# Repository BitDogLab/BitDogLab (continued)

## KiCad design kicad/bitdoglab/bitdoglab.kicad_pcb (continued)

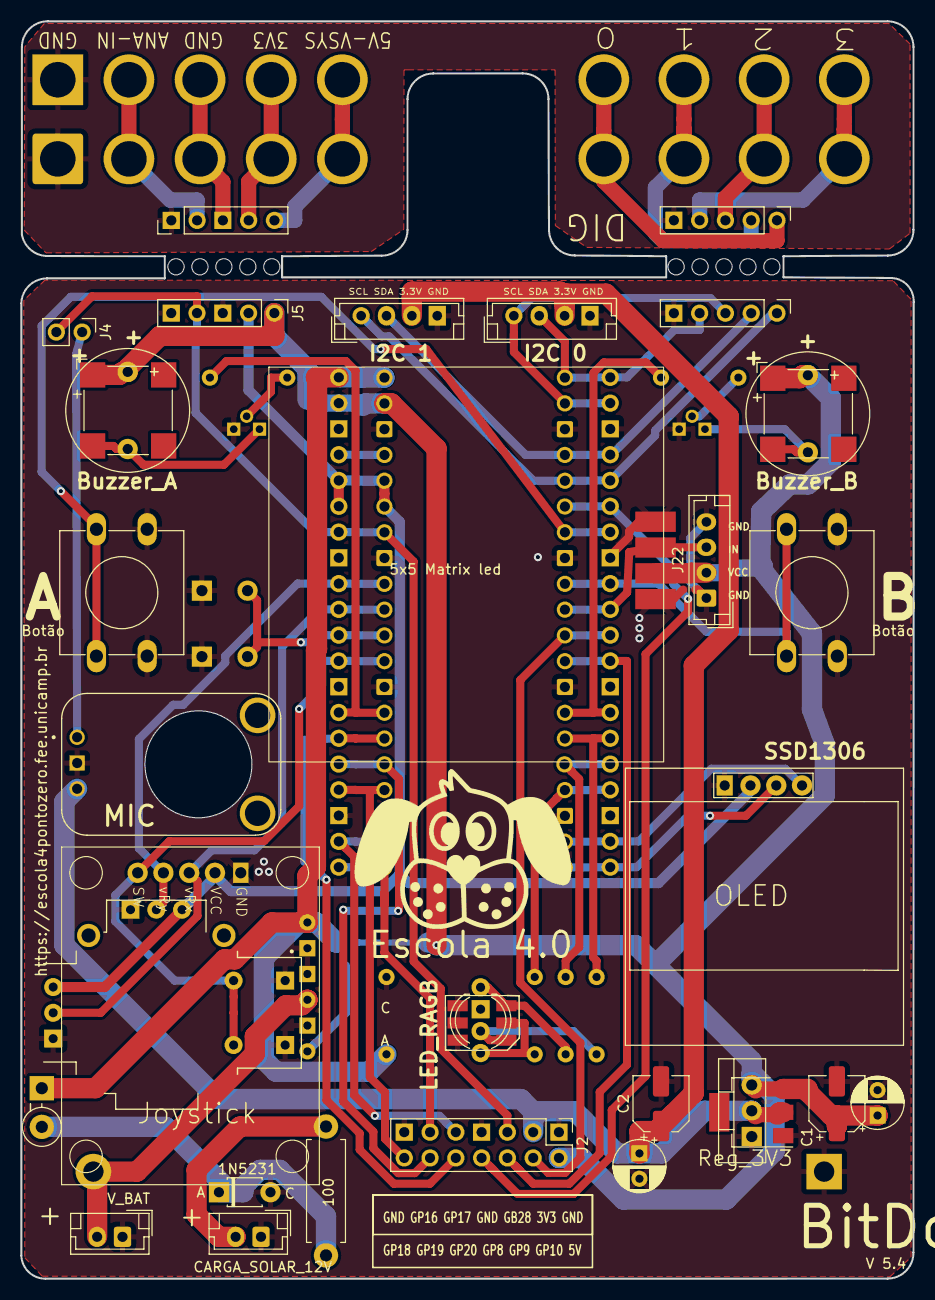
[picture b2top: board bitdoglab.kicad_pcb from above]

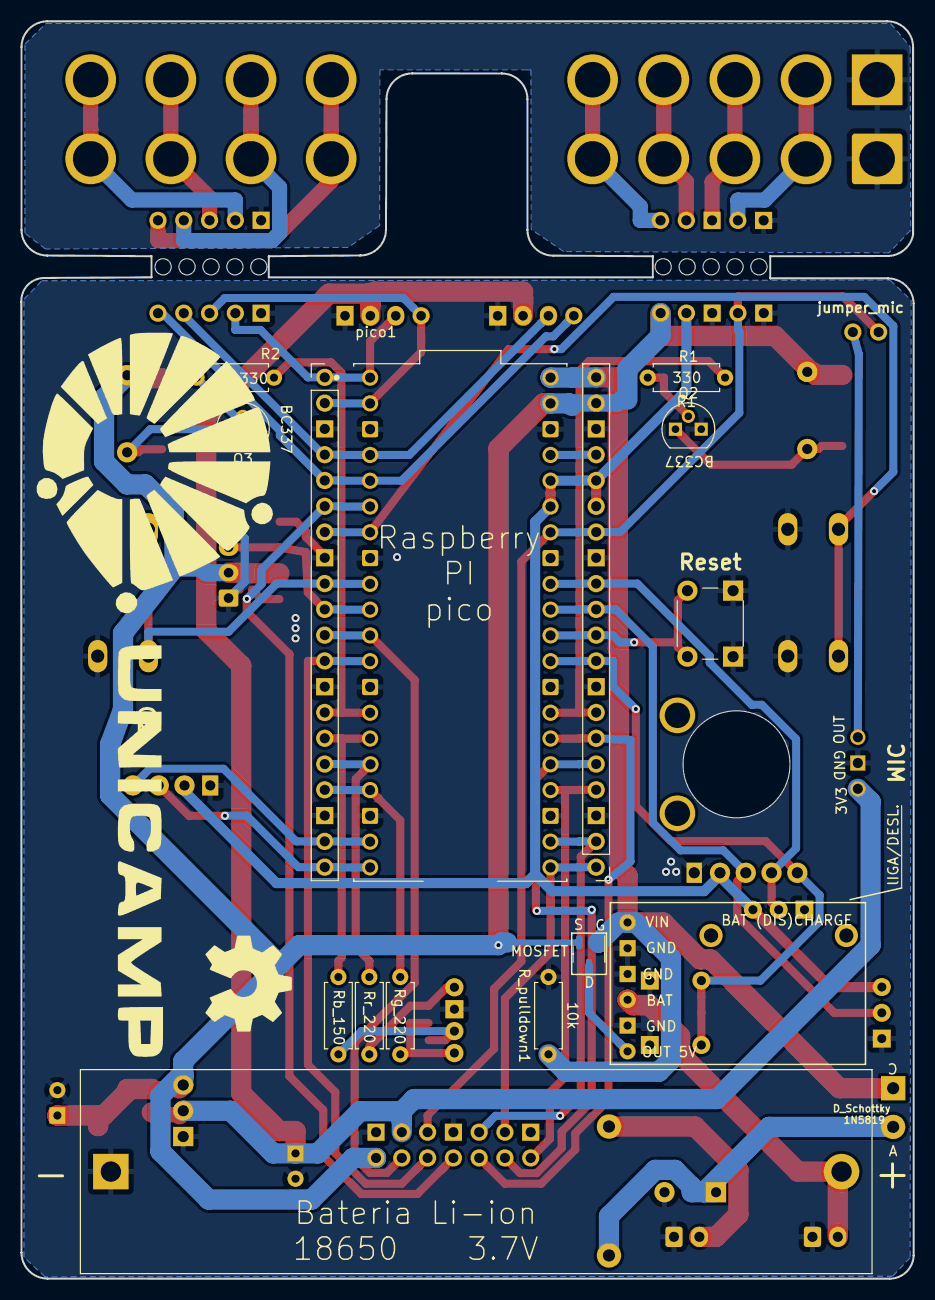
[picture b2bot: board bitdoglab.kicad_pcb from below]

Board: 2 copper layers, 87.9 x 123.9 mm, 60 parts (17 on the bottom side), 54 nets.

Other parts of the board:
G1: LOGO; logo bitDog 25mm
G2: LOGO; unicamp V2A
G3: LOGO
JOY1: JOYSTICK; XDCR_COM-09032

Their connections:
3.3_OUT: JOY1.H1, JOY1.V1; also elsewhere on the board
/pino_29: JOY1.B2A, JOY1.B2B; also elsewhere on the board
/pino_31: JOY1.H2; also elsewhere on the board
/pino_32: JOY1.V2; also elsewhere on the board
GNDREF: JOY1.B1A, JOY1.B1B, JOY1.H3, JOY1.V3; also elsewhere on the board

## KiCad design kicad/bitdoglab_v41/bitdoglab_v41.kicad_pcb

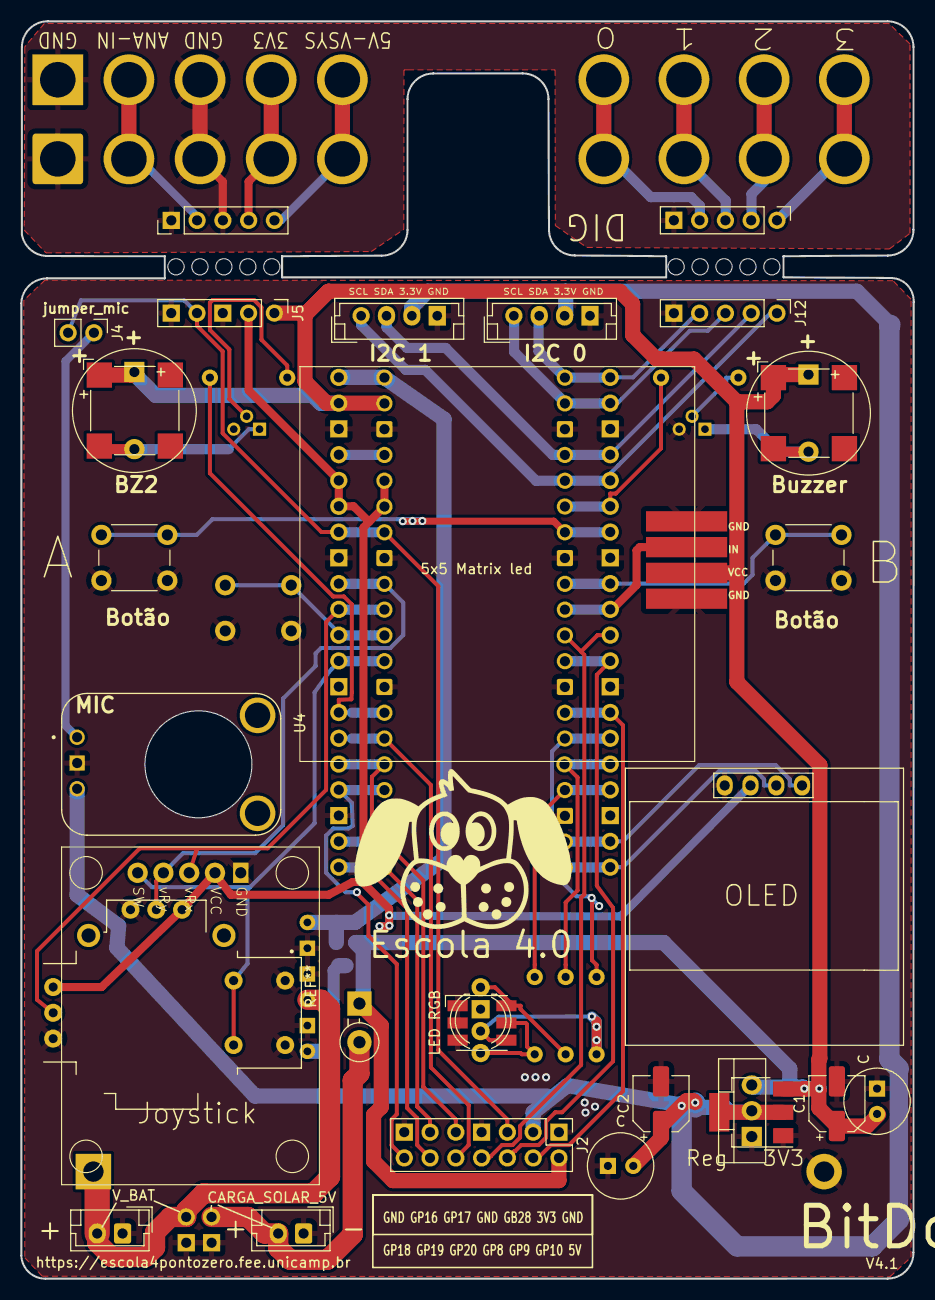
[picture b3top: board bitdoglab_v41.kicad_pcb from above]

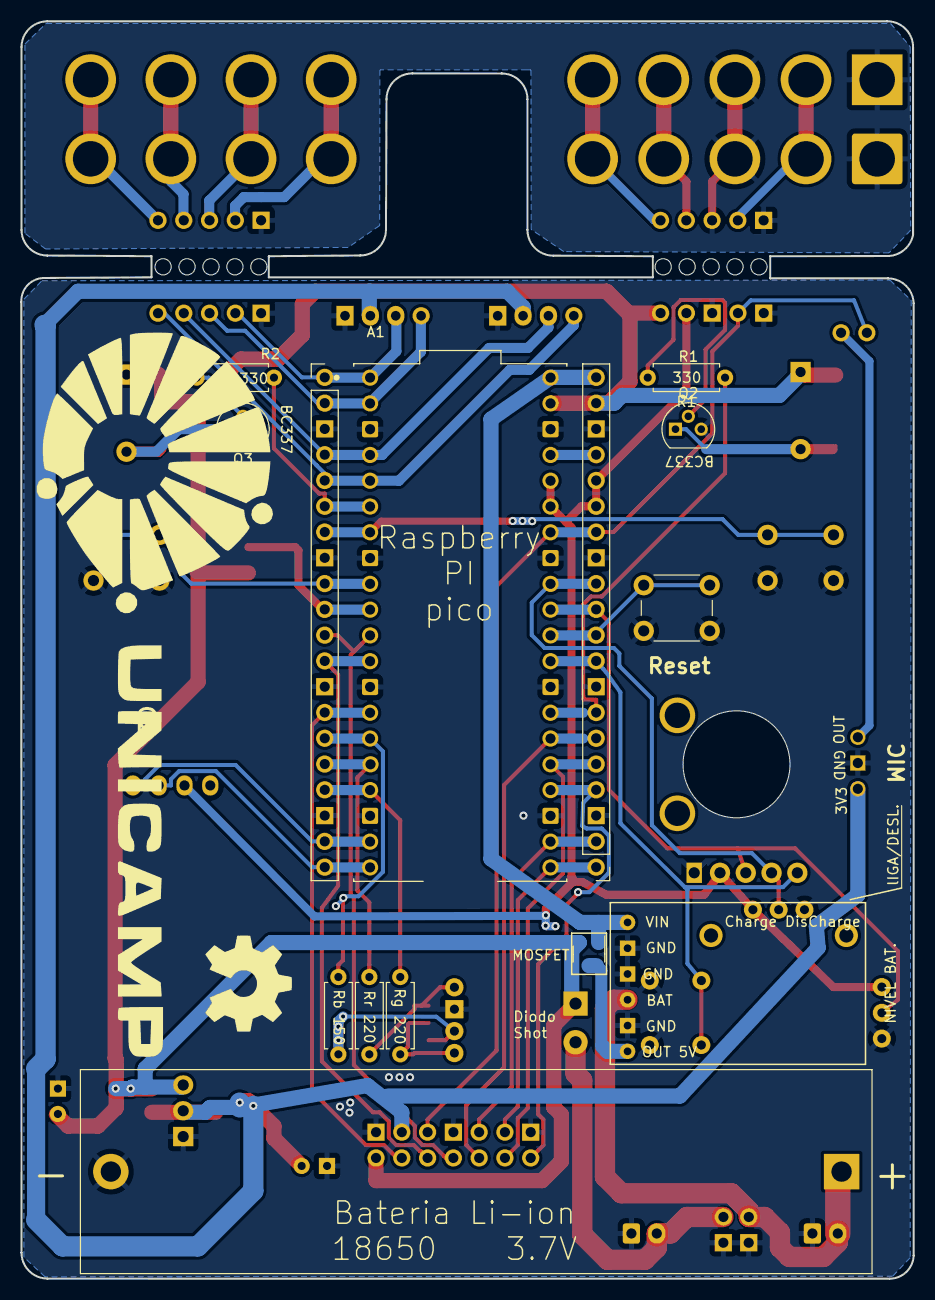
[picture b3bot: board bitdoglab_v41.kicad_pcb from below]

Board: 2 copper layers, 87.9 x 123.9 mm, 59 parts (16 on the bottom side), 52 nets.

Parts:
A1: SC0918; MODULE_SC0918
BT1: Battery_Cell; BatteryHolder_MPD_BH-18650-PC2
BZ1: Buzzer_A; Buzzer_12x9.5RM7.6
BZ2: Buzzer_A_SMD; MagneticBuzzer_CUI_CMT-8504-100-SMT
BZ3: Buzzer_B; Buzzer_12x9.5RM7.6
BZ4: Buzzer_B_SMD; MagneticBuzzer_CUI_CMT-8504-100-SMT
C: C_Radial_D6.3mm_H7.0mm_P2.50mm
C1, C2: C_Polarized_Small; CP_Elec_5x5.9
C#2: C_Radial_D6.3mm_H7.0mm_P2.50mm
CARGA_SOLAR_5V: JST_EH_B2B-EH-A_1x02_P2.50mm_Vertical
Charge DisCharge: BAT (DIS)CHARGE; Charger2A
D2: LED_RAGB; LED_D5.0mm-4_RGB_Wide_Pins
Diode Shottky: D_DO-15_P3.81mm_Vertical_KathodeUp
G1: LOGO; logo bitDog 25mm
G2: LOGO; unicamp V2A
G3: LOGO
J1, J3: Conn_01x20_Socket; PinHeader_1x20_P2.54mm_Vertical
J2: conector_idc; PinHeader_2x07_P2.54mm_Vertical
J4: jumper_mic; PinHeader_1x02_P2.54mm_Vertical
J5, J6, J12, J13: Conn_01x05_Pin; PinHeader_1x05_P2.54mm_Vertical
J7, J9: GND; SolderWire-2sqmm_1x02_P7.8mm_D2mm_OD3.9mm
J8: ANA-IN; SolderWire-2sqmm_1x02_P7.8mm_D2mm_OD3.9mm
J10: 3V3; SolderWire-2sqmm_1x02_P7.8mm_D2mm_OD3.9mm
J11: 5V-VSYS; SolderWire-2sqmm_1x02_P7.8mm_D2mm_OD3.9mm
J14: 5x5 Matrix led; Ws2812_led_5050_rgb_5x5
J15: 0; SolderWire-2sqmm_1x02_P7.8mm_D2mm_OD3.9mm
J16: 1; SolderWire-2sqmm_1x02_P7.8mm_D2mm_OD3.9mm
J17: 2; SolderWire-2sqmm_1x02_P7.8mm_D2mm_OD3.9mm
J18: 3; SolderWire-2sqmm_1x02_P7.8mm_D2mm_OD3.9mm
J19: JOYSTICK; ky-023
J100, J101: JST_EH_B4B-EH-A_1x04_P2.50mm_Vertical
LED RGB: LED_RGB_SMD; LED_RGB_5050-6
OLED: SSD1306; 128x64OLED
Q1: DMG2305UX-13; SOT-23-3
Q2, Q3: BC337; TO-92
R1, R2: 330; R_Axial_DIN0207_L6.3mm_D2.5mm_P7.62mm_Horizontal
Rb 150: 150; R_Axial_DIN0207_L6.3mm_D2.5mm_P7.62mm_Horizontal
Reg   3V3: 3.3v_smd; SOT-223
Rg 220: 150; R_Axial_DIN0207_L6.3mm_D2.5mm_P7.62mm_Horizontal
Rr 220: 220; R_Axial_DIN0207_L6.3mm_D2.5mm_P7.62mm_Horizontal
SW1: Reset; SW_PUSH_6mm
SW2: Botão; SW_PUSH_6mm
SW3: Button_B; SW_PUSH_6mm
U1: 3.3v_tht; TO-220-3_Vertical
U4: MIC; MODULE_1063
V_BAT: JST_EH_B2B-EH-A_1x02_P2.50mm_Vertical
a100, a101, a102, a103: (no value)

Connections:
3.3_OUT: A1.35 (ADC_VREF), A1.36 (3V3_OUT), J3.15, J3.16, J5.2, J19.2, OLED.2 (VCC)
3.3_OUT_EXT: J6.4, J10.1, J10.2
+3.3V: C.2, C2.1, J2.3, J100.3, J101.3, Reg 3V3.2 (GND), Reg 3V3.4, U1.2, U4.3 (VCC)
/AGND_EXT: J6.1, J6.3, J7.1, J7.2, J9.1, J9.2, J13.5
/GP0: A1.1 (GP0), J1.1, J12.4, J101.2
/GP0_EXT: J13.4, J15.1, J15.2
/GP01: A1.2 (GP1), J1.2, J12.3, J101.1
/GP01_EXT: J13.3, J16.1, J16.2
/GP02: A1.4 (GP2), J1.4, J12.2, J100.2
/GP02_EXT: J13.2, J17.1, J17.2
/GP03: A1.5 (GP3), J1.5, J12.1, J100.1
/GP03_EXT: J13.1, J18.1, J18.2
/GP04: A1.6 (GP4), J1.6, R2.1
/GP08: A1.11 (GP8), J1.11, J2.8
/GP09: A1.12 (GP9), J1.12, J2.6
/GP10: A1.14 (GP10), J1.14, J2.4
/GP11: A1.15 (GP11), J1.15, Rb 150.2
/GP12: A1.16 (GP12), J1.16, Rr 220.2
/GP13: A1.17 (GP13), J1.17, Rg 220.2
/GP16: A1.21 (GP16), J2.11, J3.1
/GP17: A1.22 (GP17), J2.9, J3.2
/GP18: A1.24 (GP18), J2.14, J3.4
/GP19: A1.25 (GP19), J2.12, J3.5
/GP20: A1.26 (GP20), J2.10, J3.6
/GP28: A1.34 (GP28), J2.5, J3.14, J4.2, J5.4
/GP28_EXT: J6.2, J8.1, J8.2
/VSYS_EXT: J6.5, J11.1, J11.2
/in: A1.10 (GP7), J1.10, J14.2
/pino_07: A1.7 (GP5), J1.7, SW2.1
/pino_09: A1.9 (GP6), J1.9, SW3.1
/pino_19: A1.19 (GP14), J1.19, OLED.4 (SDA)
/pino_20: A1.20 (GP15), J1.20, OLED.3 (SCL)
/pino_27: A1.27 (GP21), J3.7, R1.1
/pino_29: A1.29 (GP22), J3.9, J19.5
/pino_30: A1.30 (RUN), J3.10, SW1.1
/pino_31: A1.31 (GP26), J3.11, J19.3
/pino_32: A1.32 (GP27), J3.12, J19.4
/pino_37: A1.37 (3V3_EN), J3.17
GNDREF: A1.3 (GND), A1.8 (GND), A1.13 (GND), A1.18 (GND), A1.23 (GND), A1.28 (GND), A1.33 (AGND), A1.38 (GND), BT1.2 (-), C.1, C1.2, C2.2, C#2.1, CARGA_SOLAR_5V.1, Charge DisCharge.2 (GND), Charge DisCharge.4 (GND), Charge DisCharge.5 (GND), D2.2 (K), J1.3, J1.8, J1.13, J1.18, J2.1, J2.7, J2.13, J3.3, J3.8, J3.13, J3.18, J5.3, J5.5, J12.5, J14.1, J14.4, J19.1, J100.4, J101.4, LED RGB.1 (RK), LED RGB.2 (GK), LED RGB.3 (BK), OLED.1 (GND), Q2.3 (E), Q3.3 (E), Reg 3V3.1 (IN), SW1.2, SW2.2, SW3.2, U1.1, U4.2 (GND), V_BAT.1, a100.2, a101.2
unnamed: BT1.1 (+), Charge DisCharge.3 (BAT), V_BAT.2, a102.2
unnamed: BZ1.2 (+), BZ2.2 (+), Q2.1 (C)
unnamed: BZ3.2 (+), BZ4.2 (+), Q3.1 (C)
unnamed: D2.3 (BA), LED RGB.4 (BA), Rb 150.1
unnamed: D2.4 (GA), LED RGB.5 (GA), Rg 220.1
unnamed: D2.1 (RA), LED RGB.6 (RA), Rr 220.1
unnamed: J4.1, U4.1 (OUT)
unnamed: Charge DisCharge.1 (OUT5V), Q1.3 (D)
unnamed: Q2.2 (B), R1.2
unnamed: Q3.2 (B), R2.2
Solar-in: CARGA_SOLAR_5V.2, Diode Shottky.2, a103.1
VBUS: A1.40 (VBUS), Charge DisCharge.6 (VIN), J3.20, Q1.1 (G)
VSYS: A1.39 (VSYS), BZ1.1 (-), BZ2.1 (-), BZ3.1 (-), BZ4.1 (-), C1.1, C#2.2, Diode Shottky.1, J2.2, J3.19, J5.1, J14.3, Q1.2 (S), Reg 3V3.3 (OUT), U1.3

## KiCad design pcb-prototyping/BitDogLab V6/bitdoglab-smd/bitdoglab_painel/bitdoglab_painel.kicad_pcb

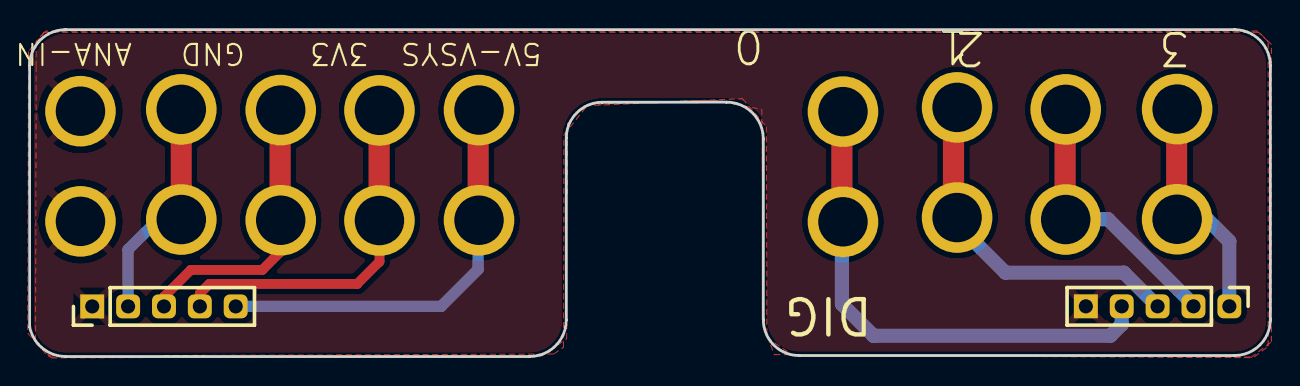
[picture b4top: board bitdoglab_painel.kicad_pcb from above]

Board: 2 copper layers, 87.8 x 23.1 mm, 11 parts (0 on the bottom side), 9 nets.

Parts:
J2, J9: Conn_01x05_Pin; PinHeader_1x05_P2.54mm_Vertical
J3, J5: GND; SolderWire-2sqmm_1x02_P7.8mm_D2mm_OD3.9mm
J4: ANA-IN; SolderWire-2sqmm_1x02_P7.8mm_D2mm_OD3.9mm
J6: 3V3; SolderWire-2sqmm_1x02_P7.8mm_D2mm_OD3.9mm
J7: 5V-VSYS; SolderWire-2sqmm_1x02_P7.8mm_D2mm_OD3.9mm
J10: 0; SolderWire-2sqmm_1x02_P7.8mm_D2mm_OD3.9mm
J11: 1; SolderWire-2sqmm_1x02_P7.8mm_D2mm_OD3.9mm
J12: 2; SolderWire-2sqmm_1x02_P7.8mm_D2mm_OD3.9mm
J13: 3; SolderWire-2sqmm_1x02_P7.8mm_D2mm_OD3.9mm

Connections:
3.3_OUT_EXT: J2.4, J6.1, J6.2
/AGND_EXT: J2.3, J5.1, J5.2
/GP0_EXT: J9.4, J13.1, J13.2
/GP01_EXT: J9.3, J12.1, J12.2
/GP02_EXT: J9.2, J11.1, J11.2
/GP03_EXT: J9.1, J10.1, J10.2
/GP28_EXT: J2.2, J4.1, J4.2
GNDREF: J2.1, J3.1, J3.2, J9.5
VSYS_EXT: J2.5, J7.1, J7.2

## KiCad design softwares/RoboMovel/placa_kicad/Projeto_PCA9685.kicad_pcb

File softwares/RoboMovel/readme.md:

# 🤖 Robô Móvel Skid-Steer — BitDogLab

Este projeto implementa o controle completo de um **robô móvel 4x4 tipo Skid-Steer** desenvolvido para a **placa BitDogLab (v6 ou v7)**.  
O robô é controlado via **Bluetooth** por aplicativos Android e utiliza um **Raspberry Pi Pico / Pico W** programado em **MicroPython**.

---

> ⚠️ **Importante:**  
> O arquivo no repositório se chama:
> ```
> movimentacaoBluetooth_buzina_luz.py
> ```
>  
> Ao enviar para a placa BitDogLab usando o **Thonny**, salve o arquivo com o nome:
> ```
> main.py
> ```
> Assim, o código será executado automaticamente quando o robô for ligado.

---

## 🧩 Lista de componentes

| Componente | Descrição |
|-------------|------------|
| **Placa BitDogLab** | Versão v6 ou v7 com Raspberry Pi Pico / Pico W |
| **Motores TT DC** | 4 motores 3–6 V com redutor e rodas de 68 mm |
| **Conexões dos motores** | 2 traseiros (master) → JST-SH 2P + jumpers fêmea soldados<br>2 dianteiros (slave) → jumpers macho soldados |
| **Chassis** | Impressão 3D em ABS — modelo v4 |
| **Mãos-francesas (suportes laterais)** | Impressas em ABS — modelo v3<br>Fixadas com **fita dupla-face** |
| **Parafusos e porcas** | 4x M3x25 + 4x M3 |
| **Ponte H** | Módulo **TB6612FNG** (integrado à PCB BitDogLab) |
| **Cabo flat IDC 2x7** | Conecta placa BitDogLab à ponte H |
| **Suporte de bateria** | 2x células 18650 Li-ion |
| **Baterias** | 2x 18650 (3.7 V) — total ~7.4 V |
| **Conector de energia** | XT30 macho |
| **Módulo Bluetooth** | HC-05 |
| **Adesivo dupla-face** | Para fixação dos suportes |

---

## 📱 Aplicativos Android compatíveis

O robô é controlado via **Bluetooth UART** usando os seguintes aplicativos (disponíveis no Google Play):

- **Arduino Bluetooth Controller** (por *Giristudio*)  
- **BT Car Controller - Arduino/ESP** (por *Giristudio*)

Ao apertar botões no aplicativo, ambos enviam comandos seriais simples (`F`, `B`, `L`, `R`, etc.) via Bluetooth.

---

## 🧠 Funcionalidades principais

| Função | Descrição |
|--------|------------|
| 🔄 **Movimento Skid-Steer 4x4** | Controle diferencial de dois lados independentes (esquerdo e direito). |
| 💡 **Controle de LEDs NeoPixel** | Iluminação RGB com ajuste de brilho e modos de luz. |
| 🔊 **Buzina sonora** | Alterna entre sons “Beep Beep” e “Foon Foon”. |
| 🔌 **Comunicação Bluetooth (UART)** | Recebe comandos em tempo real de um app Android. |
| ⚙️ **Controle de velocidade** | Ajustável de 0 a 9 (PWM). |

---

## 🪄 Sub-rotinas principais no código

O código **`movimentacaoBluetooth_buzina_luz.py`** é estruturado em funções que organizam o comportamento do robô.  
Algumas das subrotinas mais relevantes são:

| Função | Descrição |
|---------|-----------|
| `configura_pwm_motores()` | Inicializa o PWM dos motores e define o duty cycle padrão. |
| `move_frente()`, `move_tras()`, `vira_esquerda()`, `vira_direita()` | Controlam os quatro motores de forma coordenada. |
| `para_motores()` | Envia duty 0 para todos os motores (freio eletrônico). |
| `beep()` e `foon()` | Geram dois tipos distintos de som no buzzer PWM. |
| `alterna_som()` | Alterna entre os modos de buzina (“Beep” ↔ “Foon”). |
| `acende_leds(cor, brilho)` | Define a cor e intensidade dos LEDs NeoPixel. |
| `alterna_modo_luz()` | Cicla entre quatro modos de iluminação: apagado → fraco → apagado → forte. |
| `ajusta_brilho(delta)` | Aumenta ou diminui o brilho manualmente via comandos `+` e `-`. |
| `processa_comando_uart(cmd)` | Lê e executa os comandos recebidos via Bluetooth. |

---

## 🔤 Comandos via Bluetooth

| Comando | Ação |
|----------|------|
| `F` | Avança |
| `B` | Recuo |
| `L` | Vira à esquerda |
| `R` | Vira à direita |
| `S` | Para |
| `0–9` | Define velocidade (PWM) |
| `W` | Liga luz branca |
| `i` | Desliga luz |
| `I` / `X` | Alterna modos de luz |
| `+` / `-` | Ajusta brilho manualmente |
| `Y` | Alterna som da buzina |

---

## 🧱 Modelos 3D (impressão)

Os arquivos STL do robô estão disponíveis para **impressão 3D em ABS**:

| Arquivo | Função |
|----------|--------|
| `ABS_1.0070_chassis_para_4x4_v4.STL` | Chassis principal |
| `ABS_dir_1.0071_suporteBitDog_MaoFrancesa_v3.STL` | Suporte lateral direito (“mão francesa”) |
| `ABS_esq_1.0071_suporteBitDog_MaoFrancesa_v3.STL` | Suporte lateral esquerdo (“mão francesa”) |

As mãos francesas são fixadas ao chassis com **fita dupla-face**.

---

## ⚡ Alimentação

- 2x baterias **Li-ion 18650 (3.7 V)** em série → **7.4 V nominal**
- Conector **XT30**
- Corrente típica: 0.5–2 A total
- Pode ser recarregado externamente com carregador balanceado ou módulo BMS

---

## 🧰 Como gravar o programa

1. Abra o **Thonny IDE**.  
2. Conecte o Raspberry Pi Pico (BitDogLab).  
3. Abra o arquivo `movimentacaoBluetooth_buzina_luz.py`.  
4. Salve-o no dispositivo com o nome **`main.py`**.  
   - Menu: *Arquivo → Salvar como... → Raspberry Pi Pico → main.py*  
5. Reinicie a BitDogLab — o programa iniciará automaticamente.

---

## 🧪 Teste rápido

1. Conecte o módulo **HC-05** ao smartphone Android.  
2. Abra um dos aplicativos Bluetooth acima.  
3. Aperte botões da buzina e luz
4. Observe a resposta luminosa/sonora do robô.
5. Se funcionar, então você pode usar a movimentação normalmente.

---

## 🧑‍🔬 Créditos

**Projeto BitDogLab — Robô Móvel Skid-Steer**  
Campinas – SP 🇧🇷

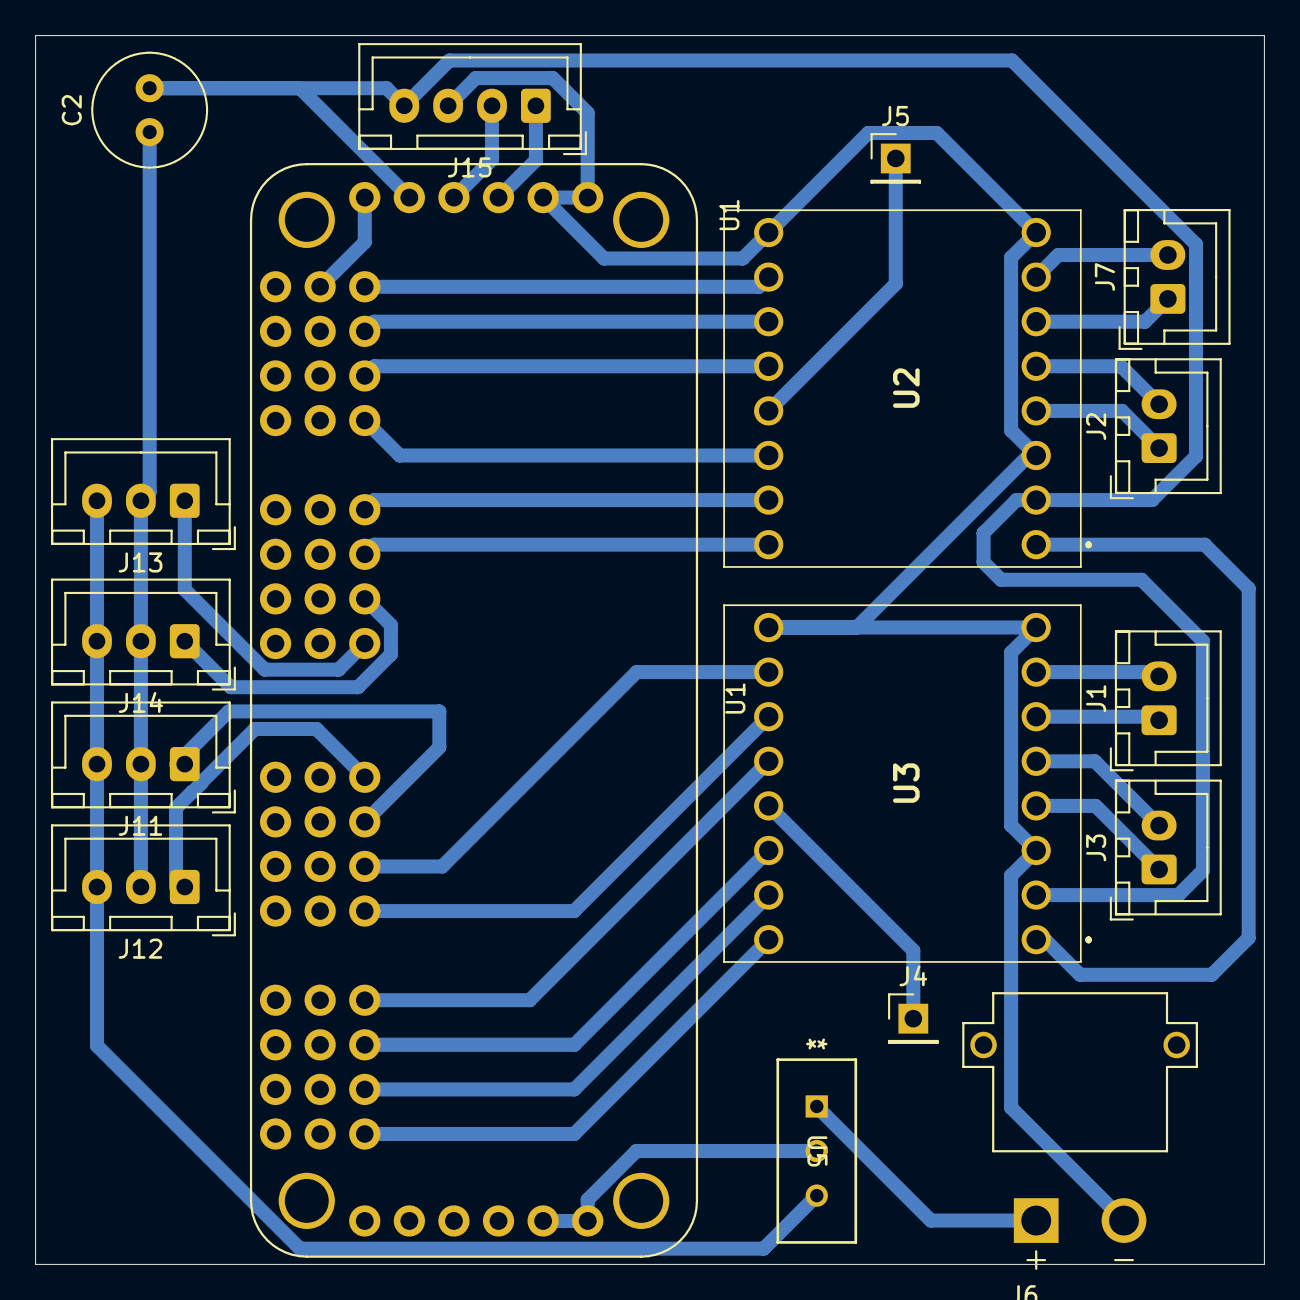
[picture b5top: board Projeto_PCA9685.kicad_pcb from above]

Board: 2 copper layers, 70.0 x 70.0 mm, 17 parts (0 on the bottom side), 33 nets.

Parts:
C2: C; C_Radial_D6.3mm_H11.0mm_P2.50mm
J1, J2, J3, J7: Conn_01x02_Pin; JST_XH_B2B-XH-A_1x02_P2.50mm_Vertical
J4, J5: Conn_01x01_Pin; PinHeader_1x01_P2.54mm_Vertical
J6: XT30-M; AMASS_XT30PW-M
J11, J12, J13, J14: Conn_01x03_Pin; JST_XH_B3B-XH-A_1x03_P2.50mm_Vertical
J15: Conn_01x04_Pin; JST_XH_B4B-XH-A_1x04_P2.50mm_Vertical
U1: 815; MODULE_815
U2, U3: ROB-14450; ROB14450
U5: MC78M06BTG; TO220-3_ONS

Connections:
+3.3V: C2.2, J15.4, U1.VCC_1 (VCC), U1.VCC_2 (VCC), U2.2 (VCC), U3.2 (VCC)
+6V: U1.V+_1 (V+), U1.V+_2 (V+), U1.V+_3 (V+), U1.V+_4 (V+), U1.V+_5 (V+), U1.V+_6 (V+), U1.V+_7 (V+), U1.V+_8 (V+), U1.V+_9 (V+), U1.V+_10 (V+), U1.V+_11 (V+), U1.V+_12 (V+), U1.V+_13 (V+), U1.V+_14 (V+), U1.V+_15 (V+), U1.V+_16 (V+), U1.V+_17 (V+), U1.V+_18 (V+)
GND: C2.1, J6.N (NEG), J11.2, J12.2, J13.2, J14.2, J15.3, U1.GND_1 (GND), U1.GND_2 (GND), U1.GND_3 (GND), U1.GND_4 (GND), U1.GND_5 (GND), U1.GND_6 (GND), U1.GND_7 (GND), U1.GND_8 (GND), U1.GND_9 (GND), U1.GND_10 (GND), U1.GND_11 (GND), U1.GND_12 (GND), U1.GND_13 (GND), U1.GND_14 (GND), U1.GND_15 (GND), U1.GND_16 (GND), U1.GND_17 (GND), U1.GND_18 (GND), U1.OE_1 (~OE), U1.OE_2 (~OE), U2.3 (GND_1), U2.8 (GND_2), U2.16 (GND_3), U3.3 (GND_1), U3.8 (GND_2), U3.16 (GND_3), U5.2 (GROUND)
unnamed: J1.1, U3.6 (B02)
unnamed: J1.2, U3.7 (B01)
unnamed: J2.1, U2.4 (A01)
unnamed: J2.2, U2.5 (A02)
unnamed: J3.1, U3.4 (A01)
unnamed: J3.2, U3.5 (A02)
unnamed: J4.1, U3.12 (STBY)
unnamed: J5.1, U2.12 (STBY)
unnamed: J6.P (POS), U2.1 (VM), U3.1 (VM), U5.1 (INPUT)
unnamed: J7.1, U2.6 (B02)
unnamed: J7.2, U2.7 (B01)
unnamed: J11.1, U1.9 (PWM_9)
unnamed: J11.3, J12.3, J13.3, J14.3, U5.3 (OUTPUT)
unnamed: J12.1, U1.8 (PWM_8)
unnamed: J13.1, U1.7 (PWM_7)
unnamed: J14.1, U1.6 (PWM_6)
unnamed: J15.1, U1.SCL_1 (SCL), U1.SCL_2 (SCL)
unnamed: J15.2, U1.SDA_1 (SDA), U1.SDA_2 (SDA)
unnamed: U1.0 (PWM_0), U2.15 (PWMB)
unnamed: U1.1 (PWM_1), U2.14 (BIN2)
unnamed: U1.2 (PWM_2), U2.13 (BIN1)
unnamed: U1.3 (PWM_3), U2.11 (AIN1)
unnamed: U1.4 (PWM_4), U2.10 (AIN2)
unnamed: U1.5 (PWM_5), U2.9 (PWMA)
unnamed: U1.10 (PWM_10), U3.15 (PWMB)
unnamed: U1.11 (PWM_11), U3.14 (BIN2)
unnamed: U1.12 (PWM_12), U3.13 (BIN1)
unnamed: U1.13 (PWM_13), U3.11 (AIN1)
unnamed: U1.14 (PWM_14), U3.10 (AIN2)
unnamed: U1.15 (PWM_15), U3.9 (PWMA)

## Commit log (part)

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2023-05-23 Add files via upload
    https://docs.google.com/spreadsheets/d/1kvooMsTfanL-sccngdAi6oykZ1CfRjh99G2syG-iSZk?usp=drive_fs
2023-05-24 Add files via upload
    KiCad file for PCI colaborative design
2023-07-24 Draft do esquematico da bitdoglab 2.0
2023-07-30 Começo da construção do layout
2023-07-30 Finalizacao do placement dos componentes
2023-07-31 roteamento e apagando backups
2023-08-01 Ajustes no roteamento
2023-08-02 Modificações no layout do professor e envio para confeccao
2023-08-02 mudança da versão do projeto para 3.0a e 3d da matrix de leds
2023-08-02 V3A mudanca do socket da barra de pinos
2023-08-31 versao 4.1 diretamente no layout
2023-09-03 Mudar VBUS para VSYS no IDC e JACARE
2023-09-10 Atualizacao do 3D da matriz de leds
2023-09-10 Adição dos gerbers da versão 4.1
2023-09-10 Remover o BOM desatualizado
2023-10-15 Add files via upload
    BOM (Bill of Material)
    https://docs.google.com/spreadsheets/d/10G9U2lKZ8DwIemRyy8-OiIrZH5e2oOeCSGOkK32-5-8/edit?usp=sharing
2023-10-25 inicio da sincronizacao do esquematico da versão 5.0
2023-10-25 Sincronizar layout com esquematico - parte 1
2023-10-26 Sincronizar layout com esquematico - parte 2
2023-10-30 Sincronizar layout com esquematico - parte 3
2024-02-04 Pacotes de libs e json para o mip install da BitDogLab 5.0
2024-02-04 Adicionando manifesto para o firmware
2024-02-04 atualizando manifestos
2024-02-04 Adicionando o Firmware da BitDogLab
2024-02-04 Atulizando o link
2024-02-24 Moved all files from kicad hardware folder to bitdoglab folder (modularized version), created a new folder for bitdoglabsmd (surface mount version) and upload all kicad project files for the smd vers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
2024-02-24 Inserted informations at README.md about the SMD v5.1 released version.
2024-02-24 Corrections of BOM spreadsheet and CSV files for version 5.1
2024-02-27 BitDogLab SMD version 5.2
2024-02-27 Readme file refactoring to account with bitdoglab v5.2 informations
2024-02-29 Versao inicial da biblioteca da matriz 5x5
2024-03-17 BitDogLab V5.3 - see release notes inside kicad/bitdoglabsmd folder
2024-03-17 pictures resize
    Resize of panel pictures from v5.3 bitdoglab smd
2024-04-01 Removendo a lista de materiais antiga
2024-04-01 Sincronizacao da placa com o esquemático
2024-04-02 versao 5.4
2024-04-02 removendo a versao 4.2
2024-04-02 create libs folder
2024-04-02 added photos and update readme
2024-04-02 change buttons footprints for 12mm
2024-04-02 Adding v5.4 release notes
2024-04-04 minor changes in firmware structure and add firmwares notes to readme
2024-04-04 minor fix in readme
2024-04-05 added softwares examples
2024-04-22 minor changes
2024-04-25 software for workshop
2024-04-26 joystick works on smd version and tests with timers
2024-04-30 Atualizacao da funcao LEDS
2024-05-03 adding templates for flask app
2024-05-08 adding matriz function
2024-05-09 update function leds
2024-05-13 rtc examples
2024-05-16 adding examples without delay
2024-05-16 uploading lora example
2024-05-16 Adding oled display
2024-05-20 updating lora softwares
2024-05-20 new examples
2024-05-20 updating softwares
2024-05-20 uploading Zaia pixelart workshop
2024-06-18 First Version - Solenoid with lora
2024-06-18 improvements server and client for solenoid
2024-06-18 Creating project Mais Plantas Mais Vidas
2024-06-27 Add files via upload
    esse arquivo é usado no projeto Mais Verde Mais Vida para comandar as válvulas solenoides na maquete úmida do projeto de irrigação
2024-07-09 Added BitDog bytearray for OLED display
    Added two bytearrays, one for a small image of BitDog (48x36) and one for a big image (80x60).
2024-07-10 Added comments to bitdog_oled.py
2024-07-13 Manual BitDogLab (Iniciando com MicroPython)
2024-07-13 Update README.md Manual BitDogLab (Iniciando com Micropython)
2024-07-13 Update README.md Manual BitDogLab (Iniciando com Micropython)
    ajuste do table of contents
2024-07-13 Update README.md BitDogLab Manual TOC
2024-07-13 Update README.md seção alternativas de gravação de firmware
2024-07-13 Update README.md com as dimensões do bitdoglab
2024-07-15 BitdogLab Retro MicroPython Game Development
2024-07-15 Update readme.md BitDogLab Pico Retro Game
2024-07-21 adicionados pico-game firmwares uf2 (pico e pico W)
2024-07-21 pico-game readme.md atualizado firmware uf2
2024-07-22 Update readme.md pico-game for rpi pico and rpi pico w
2024-08-19 1.54 inch LCD IPS display SPI for BitDogLab.
2024-10-30 Biblioteca em MicroPython dedicada para placa expansora de canais PWM e saídas lógicas da Escola 4.0.
2024-12-05 Update LICENSE to CERN-OHL-S v2.0
    Substituí a licença anterior (CC0) pela CERN Open Hardware Licence Version 2 - Strongly Reciprocal (CERN-OHL-S).
    Personalizei a licença com informações do projeto BitDogLab.
2024-12-05 Update README.md to reflect CERN-OHL-S v2.0 license
2024-12-05 Update LICENSE
2025-01-28 Exemplos da placa extensora em micropython
2025-02-11 biblioteca LoRa
    Biblioteca em Micropython LoRa
2025-02-11 Exemplos LoRa
2025-07-10 feat: README e arquivos de fabricação do módulo WIreless
2025-07-10 fix: Resolução da Imagem
2025-09-29 adiciona submodulo do app-bitdoglab
2025-10-13 initial commit robo movel
2025-10-13 luz em dois niveis e ajuste buzina
2025-10-14 initial commit do readme
2025-10-16 Atualizar o README.md
2025-11-17 adicao de arquivos TCC Arthur
2026-01-05 adicao codigo 4steer de 2025nov26 de Arthur P.S. Andrade
2026-03-24 Revise README for BitDogLab project details
    Updated the README to enhance clarity and detail about the BitDogLab project, including its educational purpose and features.
2026-03-24 Revise README for BitDogLab V7 updates
    Updated README.md to reflect changes in BitDogLab V7, including new features, programming instructions, and project structure.
2026-04-18 Add CV Lattes link for Prof. Dr. Fabiano Fruett
    Added a link to Prof. Dr. Fabiano Fruett's CV Lattes.
2026-05-11 Create images folder
2026-05-11 inclui figura
2026-06-03 chore: reorganize software folders
2026-06-03 chore: move software projects to root projects folder
2026-06-03 docs: clarify software libraries folder
2026-06-03 docs: clarify software libraries and i2c buses
2026-06-03 docs: add projects folder guide
2026-06-03 chore: organize projects by documented categories
2026-06-03 chore: add iot communication project category
2026-06-03 docs: add bitdoglab v7 getting started guide
2026-06-03 chore: remove macos metadata file
2026-06-03 docs: add bilingual getting started guide
2026-06-03 add basic MicroPython examples for BitDogLab peripherals
2026-06-03 add Basic examples
2026-06-03 reorganize PCB prototyping files and document V6 V7 hardware sources
2026-06-07 Rename figure BitDogLab.png to figure BitDogLab_1.png
2026-06-07 Rename figure_BitDogLab.png to figure_BitDogLab_1.png
2026-06-07 Rename bitdoglab figure.png to figure BitDogLab.png
2026-06-07 Rename figure BitDogLab.png to figure_BitDogLab.png
